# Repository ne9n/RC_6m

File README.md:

# 6-Meter Ham Band RC Transceiver Project

This project focuses on designing and building a modern 50MHz (6-meter) radio control system using the amateur radio bands. It features a high-power 1W transmitter and a high-sensitivity receiver, integrated into a vintage Kraft 7 transmitter case with a modern digital encoder.

## 📁 Repository Structure

### 📡 TX Hardware
- [PA_Design_Details.md](file:///TX_Hardware/PA_Design_Details.md): 1W RD01MUS2 Power Amplifier design and filtering.
- [Digital_Encoder_Conversion.md](file:///TX_Hardware/Digital_Encoder_Conversion.md): Strategy for upgrading the Kraft 7 to digital.
- [Kraft_Digital_UI_Wiring.md](file:///TX_Hardware/Kraft_Digital_UI_Wiring.md): Pinout for ESP32, ADS1115, and OLED.
- [TX_Schematic_Blueprint.md](file:///TX_Hardware/TX_Schematic_Blueprint.md): Pin-to-pin wiring for KiCad TX entry.
- [TX_BOM.md](file:///TX_Hardware/TX_BOM.md): Parts list for building the transmitter.
- [Analog_Wiring_Harness.md](file:///TX_Hardware/Analog_Wiring_Harness.md): Physical wiring for Kraft sticks and auxiliary pots.
- [Case_Modification_Guide.md](file:///TX_Hardware/Case_Modification_Guide.md): Cutting, mounting, and mechanical integration for the Kraft case.
- [Battery_Management_Design.md](file:///TX_Hardware/Battery_Management_Design.md): LiPo conversion and USB-C charging for the Kraft case.

### 🛩️ RX Hardware
- [RX_Design_Details.md](file:///RX_Hardware/RX_Design_Details.md): Front-end LNA, LT5560 upconverter (118.2MHz LO, ~169MHz IF), and Si4463 FSK receiver.
- [Receiver_Servo_Design.md](file:///RX_Hardware/Receiver_Servo_Design.md): Servo bus wiring and MCU integration.
- [RX_PCB_Design_Guide.md](file:///RX_Hardware/RX_PCB_Design_Guide.md): Physical layout, grounding, and stackup for the RX board.
- [RX_Schematic_Blueprint.md](file:///RX_Hardware/RX_Schematic_Blueprint.md): Pin-to-pin wiring for KiCad schematic entry.
- [RX_Power_Supply_Design.md](file:///RX_Hardware/RX_Power_Supply_Design.md): Servo bus filtering and 3.3V LDO design.
- [RX_BOM.md](file:///RX_Hardware/RX_BOM.md): Parts list for building the receiver.

### 💻 Software
- [Kraft_7_Firmware_Skeleton.ino](file:///Software/Kraft_7_Firmware_Skeleton.ino): Full code structure for dual ADC and Si5351 handler.
- [Firmware_Protocol_Spec.md](file:///Software/Firmware_Protocol_Spec.md): GFSK modulation logic and 50MHz packet structure.
- [Si5351_GFSK_Driver.cpp](file:///Software/Si5351_GFSK_Driver.cpp): C++ driver for frequency-pulling modulation.
- [Firmware_Implementation.md](file:///Software/Firmware_Implementation.md): GFSK modulation and Si4463 packet reception over SPI.
- [Trim_Implementation.md](file:///Software/Trim_Implementation.md): Digital trim logic and math.
- [Project_Recommendations.md](file:///Software/Project_Recommendations.md): ELRS and SimpleTX project guidance.
- [Telemetry_Protocol_Design.md](file:///Software/Telemetry_Protocol_Design.md): 2-way 50MHz data packet definition.

### 📜 System Documentation
- [System_Requirements.md](file:///System_Docs/System_Requirements.md): High-level project specifications and architectural goals.
- [6m_ham_rc_transceiver_design.md](file:///System_Docs/6m_ham_rc_transceiver_design.md): System architecture and block diagrams.
- [Initial_BOM.md](file:///System_Docs/Initial_BOM.md): Complete parts list for ordering.
- [PCB_Layout_Strategy.md](file:///C:/radio/System_Docs/PCB_Layout_Strategy.md): RF grounding and isolation rules.
- [PCB_Footprint_Guide.md](file:///C:/radio/System_Docs/PCB_Footprint_Guide.md): SMT footprints and assembly instructions.
- [PCB_Footprint_Mapping.md](file:///C:/radio/System_Docs/PCB_Footprint_Mapping.md): KiCad library mapping for all BOM parts.
- [RF_Range_Analysis.md](file:///C:/radio/System_Docs/RF_Range_Analysis.md): Theoretical range and link budget for 1W on 50MHz.
- **Datasheets**:
    - [SPF5043Z.pdf](file:///C:/radio/System_Docs/Datasheets/SPF5043Z.pdf): High-performance GaAs pHEMT MMIC LNA (50-4000 MHz).
    - [Murata_SFE_10.7_Reference.md](file:///C:/radio/System_Docs/Datasheets/Murata_SFE_10.7_Reference.md): Technical specs for the 10.7MHz IF Ceramic Filter. *Superseded (2026-09-28): the 10.7MHz IF was replaced by a ~169MHz IF into an Si4463.*
- **KiCad Projects**:
    - [TX_50MHz_1W.kicad_sch](file:///C:/radio/KiCad_Projects/TX_50MHz_1W/TX_50MHz_1W.kicad_sch): Main Transmitter Schematic.
    - [RX_50MHz_SDR.kicad_sch](file:///C:/radio/KiCad_Projects/RX_50MHz_SDR/RX_50MHz_SDR.kicad_sch): Main Receiver Schematic.
    - [RX_50MHz_SDR.net](file:///C:/radio/KiCad_Projects/RX_50MHz_SDR/RX_50MHz_SDR.net): Netlist for Receiver layout.
    - [TX_50MHz_1W.net](file:///C:/radio/KiCad_Projects/TX_50MHz_1W/TX_50MHz_1W.net): Netlist for Transmitter layout.
    - [KiCad_Import_Instructions.md](file:///C:/radio/KiCad_Projects/KiCad_Import_Instructions.md): Step-by-step guide to building the boards.

---

## 🛠️ Project Goals
1.  **2-Way Communication**: Telemetry feedback (Battery, RSSI) from plane to transmitter.
2.  **High Power**: 1W output for superior range and reliability on the 50MHz band.
3.  **Modern Digital Link**: Moving away from old analog PPM to a robust GFSK digital protocol (ELRS-inspired).
4.  **Vintage Aesthetic**: Preserving the classic feel of the Kraft 7 transmitter while providing modern performance.

---
*Maintained by ne9n.*

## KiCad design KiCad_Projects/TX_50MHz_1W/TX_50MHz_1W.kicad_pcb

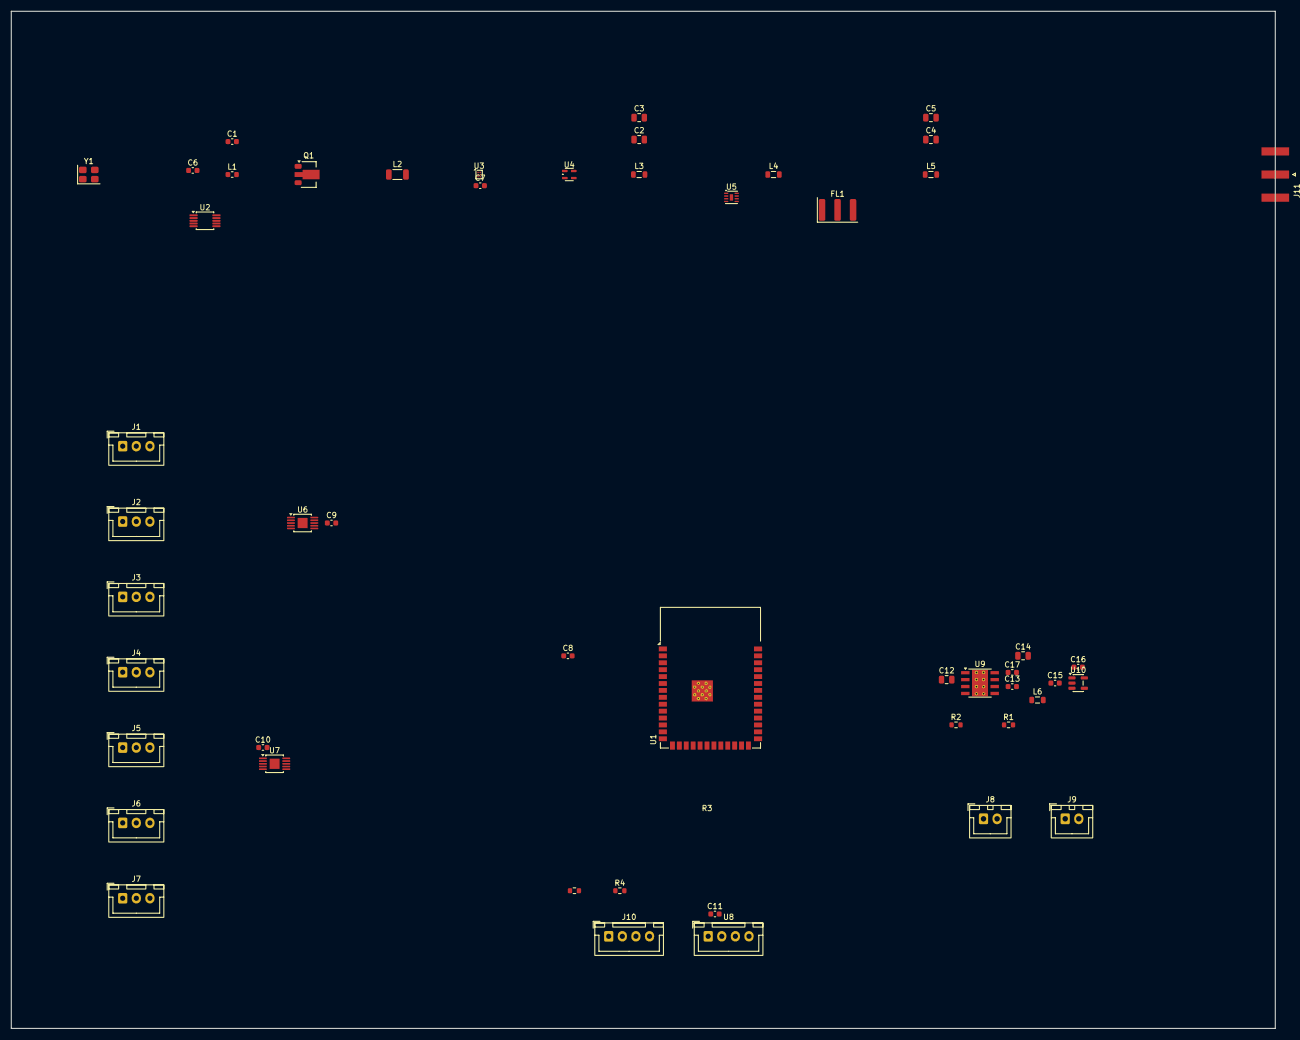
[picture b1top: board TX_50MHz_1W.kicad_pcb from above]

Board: 2 copper layers, 232.3 x 186.9 mm, 51 parts (0 on the bottom side), 32 nets, no tracks yet.

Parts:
C1, C17: 10nF; C_0603_1608Metric
C2, C5: 120pF; C_0805_2012Metric
C3, C4: 220pF; C_0805_2012Metric
C6, C7, C8, C9, C10, C11: 0.1uF; C_0603_1608Metric
C12: 10uF; C_0805_2012Metric
C13, C15, C16: 1uF; C_0603_1608Metric
C14: 22uF; C_0805_2012Metric
FL1: 10.7MHz Murata SFE; Resonator_SMD_Murata_SFECV-3Pin_6.9x2.9mm
J1: AIL Stick; JST_XH_B3B-XH-A_1x03_P2.50mm_Vertical
J2: ELE Stick; JST_XH_B3B-XH-A_1x03_P2.50mm_Vertical
J3: THR Stick; JST_XH_B3B-XH-A_1x03_P2.50mm_Vertical
J4: RUD Stick; JST_XH_B3B-XH-A_1x03_P2.50mm_Vertical
J5: AUX6; JST_XH_B3B-XH-A_1x03_P2.50mm_Vertical
J6: AUX5; JST_XH_B3B-XH-A_1x03_P2.50mm_Vertical
J7: AUX7; JST_XH_B3B-XH-A_1x03_P2.50mm_Vertical
J8: V_BATT In (XT30); JST_XH_B2B-XH-A_1x02_P2.50mm_Vertical
J9: 5V Logic In; JST_XH_B2B-XH-A_1x02_P2.50mm_Vertical
J10: I2C Exp / OLED; JST_XH_B4B-XH-A_1x04_P2.50mm_Vertical
J11: ANT; SMA_Amphenol_132289_EdgeMount
L1: 150nH; L_0603_1608Metric
L2: 1.0uH (RFC); L_1206_3216Metric
L3, L4, L5: 180nH; L_0805_2012Metric
L6: 10uH; L_0805_2012Metric
Q1: RD01MUS2 (1W PA); SOT-89-3
R1: 40.2k; R_0603_1608Metric
R2: 10.2k; R_0603_1608Metric
R3, R4: 4.7k; R_0603_1608Metric
U1: ESP32-S3-WROOM-1-N16R8; ESP32-S3-WROOM-1
U2: Si5351A-B-GT; MSOP-10_3x3mm_P0.5mm
U3: BGS12SN6E6327XTSA1 (T/R SW); Infineon_PG-TSNP-6-10_0.7x1.1mm_0.7x1.1mm_P0.4mm
U4: SPF5043Z (LNA); SOT-343_SC-70-4
U5: LT5560 (Mixer); DFN-8-1EP_2x2mm_P0.5mm_EP0.6x1.2mm
U6: ADS1115IDGSR (0x48); HVSSOP-10-1EP_3x3mm_P0.5mm_EP1.83x1.89mm
U7: ADS1115IDGSR (0x49); HVSSOP-10-1EP_3x3mm_P0.5mm_EP1.83x1.89mm
U8: SH1106 1.3in OLED; JST_XH_B4B-XH-A_1x04_P2.50mm_Vertical
U9: LMR33630BDDA; Texas_HSOP-8-1EP_3.9x4.9mm_P1.27mm_ThermalVias
U10: AP2112K-3.3TRG1; SOT-23-5
Y1: 26.000MHz; Crystal_SMD_3225-4Pin_3.2x2.5mm

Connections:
5V: C14.2, C15.2, J9.1, L6.2, R1.1, U7.7, U10.1, U10.3
+3V3: C6.1, C7.1, C8.1, C9.1, C10.1, C11.1, C16.2, J1.1, J2.1, J3.1, J4.1, J5.1, J6.1, J7.1, J10.1, R3.1, R4.1, U1.2, U1.3, U2.1, U2.9, U3.4, U5.3, U5.4, U6.8, U7.1, U7.8, U8.1, U10.5
ADC_IN: FL1.3, U1.13
GND: C2.1, C3.1, C3.2, C4.1, C5.1, C6.2, C7.2, C8.2, C9.2, C10.2, C11.2, C12.1, C13.2, C14.1, C15.1, C16.1, FL1.2, J1.3, J2.3, J3.3, J4.3, J5.3, J6.3, J7.3, J8.2, J9.2, J10.2, J11.2, L3.2, L4.1, Q1.2, R2.2, U1.1, U1.41, U2.10, U3.2, U4.2, U4.4, U5.2, U5.6, U5.8, U5.9, U6.1, U6.3, U7.3, U8.2, U9.1, U9.9, U10.2
unnamed: C1.2, L1.1
unnamed: C4.2, L4.2, L5.1
unnamed: FL1.1, U5.5
unnamed: J1.2, U6.4
unnamed: J2.2, U6.5
unnamed: J3.2, U6.6
unnamed: J4.2, U6.7
unnamed: J5.2, U7.4
unnamed: J6.2, U7.5
unnamed: J7.2, U7.6
unnamed: J10.3, R3.2, U1.12, U2.4, U6.10, U7.9, U8.3
unnamed: J10.4, R4.2, U1.11, U2.5, U6.9, U7.10, U8.4
unnamed: C5.2, J11.1, L5.2
unnamed: L2.1, Q1.3, U3.3
unnamed: L1.2, Q1.1
unnamed: U1.14, U3.6
unnamed: C1.1, U2.6
unnamed: U2.7, U5.7
unnamed: U2.2, Y1.1
unnamed: U2.3, Y1.2
unnamed: U3.1, U4.1
unnamed: C2.2, L3.1, U3.5
unnamed: U4.3, U5.1
unnamed: C17.2, U9.7
unnamed: R1.2, R2.1, U9.5
unnamed: C17.1, L6.1, U9.8
unnamed: C13.1, U9.6
V_BATT: C12.2, J8.1, L2.2, U9.2, U9.3

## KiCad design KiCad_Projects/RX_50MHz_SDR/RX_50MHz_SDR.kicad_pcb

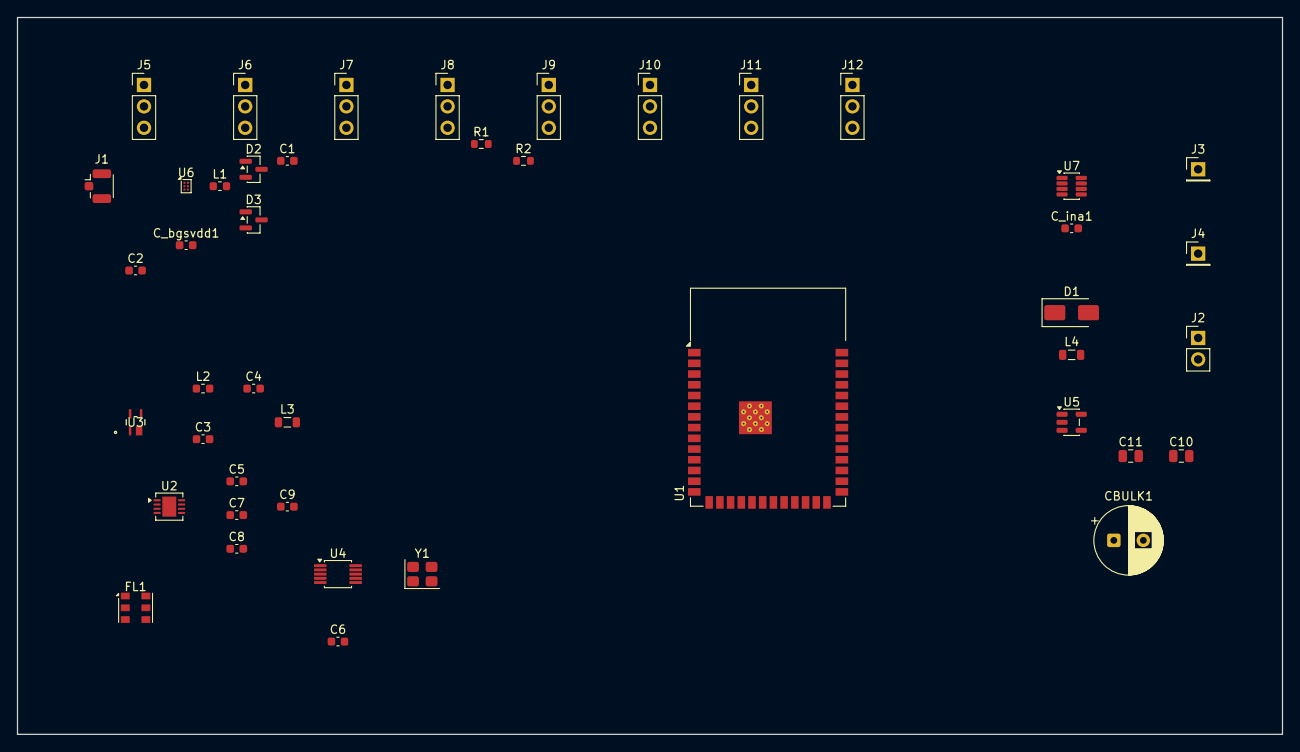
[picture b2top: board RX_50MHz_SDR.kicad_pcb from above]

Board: 2 copper layers, 150.0 x 85.0 mm, 44 parts (0 on the bottom side), 35 nets, no tracks yet.

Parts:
C1, C2, C3, C5, C8: 100pF; C_0603_1608Metric
C4, C6, C7: 10nF; C_0603_1608Metric
C9: 0.1uF; C_0603_1608Metric
C10, C11: 10uF; C_0805_2012Metric
CBULK1: 470uF; CP_Radial_D8.0mm_P3.50mm
C_bgsvdd1: 0.1uF; C_0603_1608Metric
C_ina1: 0.1uF; C_0603_1608Metric
D1: SS14; D_SMA
D2, D3: BAV99; SOT-23
FL1: 10.7MHz; Filter_Murata_SFECF-6
J1: ANTENNA; U.FL_Hirose_U.FL-R-SMT-1_Vertical
J2: SERVO_5V_IN; PinHeader_1x02_P2.54mm_Vertical
J3: BATT+; PinHeader_1x01_P2.54mm_Vertical
J4: ESC+; PinHeader_1x01_P2.54mm_Vertical
J5: SERVO1; PinHeader_1x03_P2.54mm_Vertical
J6: SERVO2; PinHeader_1x03_P2.54mm_Vertical
J7: SERVO3; PinHeader_1x03_P2.54mm_Vertical
J8: SERVO4; PinHeader_1x03_P2.54mm_Vertical
J9: SERVO5; PinHeader_1x03_P2.54mm_Vertical
J10: SERVO6; PinHeader_1x03_P2.54mm_Vertical
J11: SERVO7; PinHeader_1x03_P2.54mm_Vertical
J12: SERVO8; PinHeader_1x03_P2.54mm_Vertical
L1, L2: 220nH; L_0603_1608Metric
L3: 1uH; L_0805_2012Metric
L4: 10uH; L_0805_2012Metric
R1, R2: 4.7k; R_0603_1608Metric
U1: ESP32-S3-WROOM-1
U2: LT5560EDD#PBF; DFN-8-1EP_3x3mm_P0.5mm_EP1.65x2.38mm
U3: SPF5043Z; SPF5043Z_QOR
U4: Si5351A-B-GT; MSOP-10_3x3mm_P0.5mm
U5: AP2112K-3.3TRG1; SOT-23-5
U6: BGS12PL6; Infineon_PG-TSNP-6-10_0.7x1.1mm_0.7x1.1mm_P0.4mm
U7: INA219AIDCNR; SOT-23-8
Y1: 26MHz; Crystal_SMD_3225-4Pin_3.2x2.5mm

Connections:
3V3: C6.1, C9.1, C11.1, C_bgsvdd1.1, C_ina1.1, L3.2, R1.1, R2.1, U1.2 (3V3), U1.3 (EN), U2.4 (VCC), U4.1 (VDD), U5.5 (VOUT), U6.6 (VDD), U7.4 (VS)
5V_RAIL: CBULK1.1, D1.1, J2.1, J5.2 (VCC), J6.2 (VCC), J7.2 (VCC), J8.2 (VCC), J9.2 (VCC), J10.2 (VCC), J11.2 (VCC), J12.2 (VCC)
/ADC_IF: FL1.3 (OUT), U1.4 (IO4)
/ANT: J1.1, U6.5 (ANT)
/BATT_POS: J3.1 (1_1), U7.1 (IN+)
/ESC_POS: J4.1 (1_1), U7.2 (IN-)
/LNA_IN: C2.2, D2.1, D3.2, L1.1, U3.3 (RF_IN)
/LNA_OUT_M: C3.1, L2.2
/LNA_OUT_VCC: C4.1, L2.1, L3.1, U3.1 (RF_OUT)
/LO_CLK0: U2.7 (LO+), U4.6 (CLK0)
/MIX_IN_N: C5.1, U2.2 (IN-)
/MIX_LO_N: C8.1, U2.8 (LO-)
/MIX_OUT_N: C7.1, U2.6 (OUT-)
/RF1_NET: C2.1, U6.3 (RF1)
/RX_EN: U1.20 (IO12), U2.3 (EN)
/SCL: R2.2, U1.17 (IO9), U4.4 (SCL), U7.5 (SCL)
/SDA: R1.2, U1.12 (IO8), U4.5 (SDA), U7.6 (SDA)
/SERVO1_SIG: J5.1 (SIG), U1.9 (IO16)
/SERVO2_SIG: J6.1 (SIG), U1.5 (IO5)
/SERVO3_SIG: J7.1 (SIG), U1.6 (IO6)
/SERVO4_SIG: J8.1 (SIG), U1.7 (IO7)
/SERVO5_SIG: J9.1 (SIG), U1.8 (IO15)
/SERVO6_SIG: J10.1 (SIG), U1.10 (IO17)
/SERVO7_SIG: J11.1 (SIG), U1.11 (IO18)
/SERVO8_SIG: J12.1 (SIG), U1.18 (IO10)
/TELEM_TX_PRE: C1.2, U6.1 (RF2)
/TELEM_TX_PRE_B: C1.1, U4.7 (CLK1)
/TR_SW: U1.19 (IO11), U6.4 (CTRL)
/VIN_FILT: D1.2, L4.1
/VIN_LDO: C10.1, L4.2, U5.1 (VIN), U5.3 (EN)
/XTAL_A: U4.2 (XA), Y1.1
/XTAL_B: U4.3 (XB), Y1.2
GND: C4.2, C5.2, C6.2, C7.2, C8.2, C9.2, C10.2, C11.2, CBULK1.2, C_bgsvdd1.2, C_ina1.2, D2.2, D3.1, FL1.2 (GND), J1.2, J2.2, J5.3 (GND), J6.3 (GND), J7.3 (GND), J8.3 (GND), J9.3 (GND), J10.3 (GND), J11.3 (GND), J12.3 (GND), L1.2, U1.1 (GND), U2.9 (EP), U3.2 (GND), U3.4 (GND), U4.8 (GND), U5.2 (GND), U6.2 (GND), U7.3 (GND), U7.7 (A0), U7.8 (A1)
unnamed: FL1.1 (IN), U2.5 (OUT+)
unnamed: C3.2, U2.1 (IN+)

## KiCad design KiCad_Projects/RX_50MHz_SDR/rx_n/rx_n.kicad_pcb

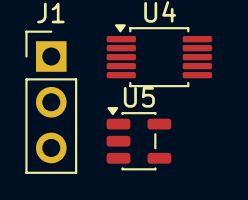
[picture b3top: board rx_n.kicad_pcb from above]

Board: 2 copper layers, 3 parts (0 on the bottom side), 2 nets, no tracks yet.

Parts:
J1: Servo_1; PinHeader_1x03_P2.54mm_Vertical
U4: Si5351A; MSOP-10_3x3mm_P0.5mm
U5: AP2112K-3.3; SOT-23-5

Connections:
+3V3: U4.1, U5.5
GND: J1.3, U4.7, U5.2

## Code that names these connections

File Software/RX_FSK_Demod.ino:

/*
 * 50MHz RC Receiver - IF-undersampling FSK demodulator (ESP32-S3)
 *
 * Implements RX_Design_Details.md / Firmware_Implementation.md section 2:
 *   Undersample IF -> digital down-conversion (I/Q) -> phase discriminator -> bit slicer.
 *
 * IMPORTANT -- read before wiring this to the real IF filter:
 * The ESP32-S3's ADC continuous-mode driver is hardware-capped at
 * SOC_ADC_SAMPLE_FREQ_THRES_HIGH = 83,333 Hz (esp32s3/soc_caps.h), not the 2.5Msps the
 * design doc assumed. That's fine for the FSK signal itself (Carson's-rule bandwidth is
 * only ~15kHz at 5kHz deviation / 2400 baud), but the BOM's 10.7MHz ceramic filter
 * (Murata SFE, ~230kHz bandwidth) is far wider than this ADC can Nyquist-sample without
 * aliasing -- everything within that 230kHz window folds into the decoded signal as noise.
 * Before relying on this: either narrow the IF filter to roughly match the FSK signal's
 * occupied bandwidth (~20-30kHz), or add an analog discriminator ahead of the ADC instead
 * of undersampling the raw IF. See chat discussion for the tradeoff.
 *
 * Library note: no off-the-shelf FSK/DSP library is used. Arduino's analogContinuous()
 * only returns *averaged* results per callback (see esp32-hal-adc.h) -- unusable for
 * per-sample I/Q down-conversion -- so this talks to the IDF adc_continuous driver
 * directly. Requires arduino-esp32 core 3.x (IDF 5.x); the classic core 2.x bundled by
 * the stock PlatformIO "espressif32" registry package predates this driver on the S3.
 */

#include <Arduino.h>
#include "esp_adc/adc_continuous.h"
#include "fsk_demod_core.h"

// ASSUMED, per the schematic's own note ("ASSUMED (not specified in source docs): ESP32
// GPIO nums for TR_SW, RX_EN, ADC_IF"). Must be an ESP32-S3 ADC1 pin (GPIO1-10). Update
// once the schematic's ADC_IF net is pinned to a real GPIO.
#ifndef ADC_IF_PIN
#define ADC_IF_PIN 4
#endif

#define SAMPLE_RATE_HZ    83106u              // 4*10.7MHz/515 -- see quarter-IF derivation below
#define IF_ALIAS_HZ       (SAMPLE_RATE_HZ / 4) // true 10.7MHz IF aliases here by construction
#define FSK_DEVIATION_HZ  5000u                // matches Si5351_GFSK_Driver.cpp
#define FSK_BAUD          2400u

/*
 * Quarter-IF sample rate derivation:
 * Bandpass/undersampling requires Fs = 4*Fif/(2k+1) for some integer k, which places the
 * alias exactly at Fs/4 -- no NCO frequency search needed, the ratio is exact by construction.
 * Solving for the largest Fs <= 83333 Hz with Fif = 10.7MHz gives k=257 -> Fs = 83106.8 Hz.
 */

static adc_continuous_handle_t s_adc_handle = nullptr;
static FskDemod s_demod(SAMPLE_RATE_HZ, IF_ALIAS_HZ, FSK_BAUD, FSK_BAUD * 3.0f);
static int32_t s_dc_offset = 2048; // TODO: measure at boot with RX_EN low, or track with a slow LPF

static bool IRAM_ATTR onConvDone(adc_continuous_handle_t handle, const adc_continuous_evt_data_t *edata, void *user_data) {
    // Just needs to exist for the driver's internal signaling; actual sample handling
    // happens in pollAdcAndDemod() via adc_continuous_read().
    return false;
}

static void setupContinuousAdc() {
    adc_unit_t unit;
    adc_channel_t channel;
    ESP_ERROR_CHECK(adc_continuous_io_to_channel(ADC_IF_PIN, &unit, &channel));

    adc_continuous_handle_cfg_t handle_cfg = {
        .max_store_buf_size = 4096,
        .conv_frame_size = 256,
    };
    ESP_ERROR_CHECK(adc_continuous_new_handle(&handle_cfg, &s_adc_handle));

    static adc_digi_pattern_config_t pattern[1] = {};
    pattern[0].atten = ADC_ATTEN_DB_11;
    pattern[0].channel = channel;
    pattern[0].unit = unit;
    pattern[0].bit_width = SOC_ADC_DIGI_MAX_BITWIDTH;

    adc_continuous_config_t dig_cfg = {
        .pattern_num = 1,
        .adc_pattern = pattern,
        .sample_freq_hz = SAMPLE_RATE_HZ,
        .conv_mode = ADC_CONV_SINGLE_UNIT_1,
        .format = ADC_DIGI_OUTPUT_FORMAT_TYPE2,
    };
    ESP_ERROR_CHECK(adc_continuous_config(s_adc_handle, &dig_cfg));

    adc_continuous_evt_cbs_t cbs = { .on_conv_done = onConvDone };
    ESP_ERROR_CHECK(adc_continuous_register_event_callbacks(s_adc_handle, &cbs, nullptr));

    ESP_ERROR_CHECK(adc_continuous_start(s_adc_handle));
}

static uint8_t s_read_buf[1024];

void pollAdcAndDemod() {
    uint32_t out_len = 0;
    esp_err_t err = adc_continuous_read(s_adc_handle, s_read_buf, sizeof(s_read_buf), &out_len, 0);
    if (err != ESP_OK) return;

    for (uint32_t i = 0; i < out_len; i += SOC_ADC_DIGI_RESULT_BYTES) {
        adc_digi_output_data_t *p = (adc_digi_output_data_t *)&s_read_buf[i];
        int32_t raw = p->type2.data;
        bool bit;
        if (s_demod.processSample(raw, s_dc_offset, &bit)) {
            // TODO: hand `bit` to a bit/byte assembler + the ELRS-style packet framer
            // described in Firmware_Implementation.md section 3.
        }
    }
}

void setup() {
    Serial.begin(115200);
    setupContinuousAdc();
}

void loop() {
    pollAdcAndDemod();
}
